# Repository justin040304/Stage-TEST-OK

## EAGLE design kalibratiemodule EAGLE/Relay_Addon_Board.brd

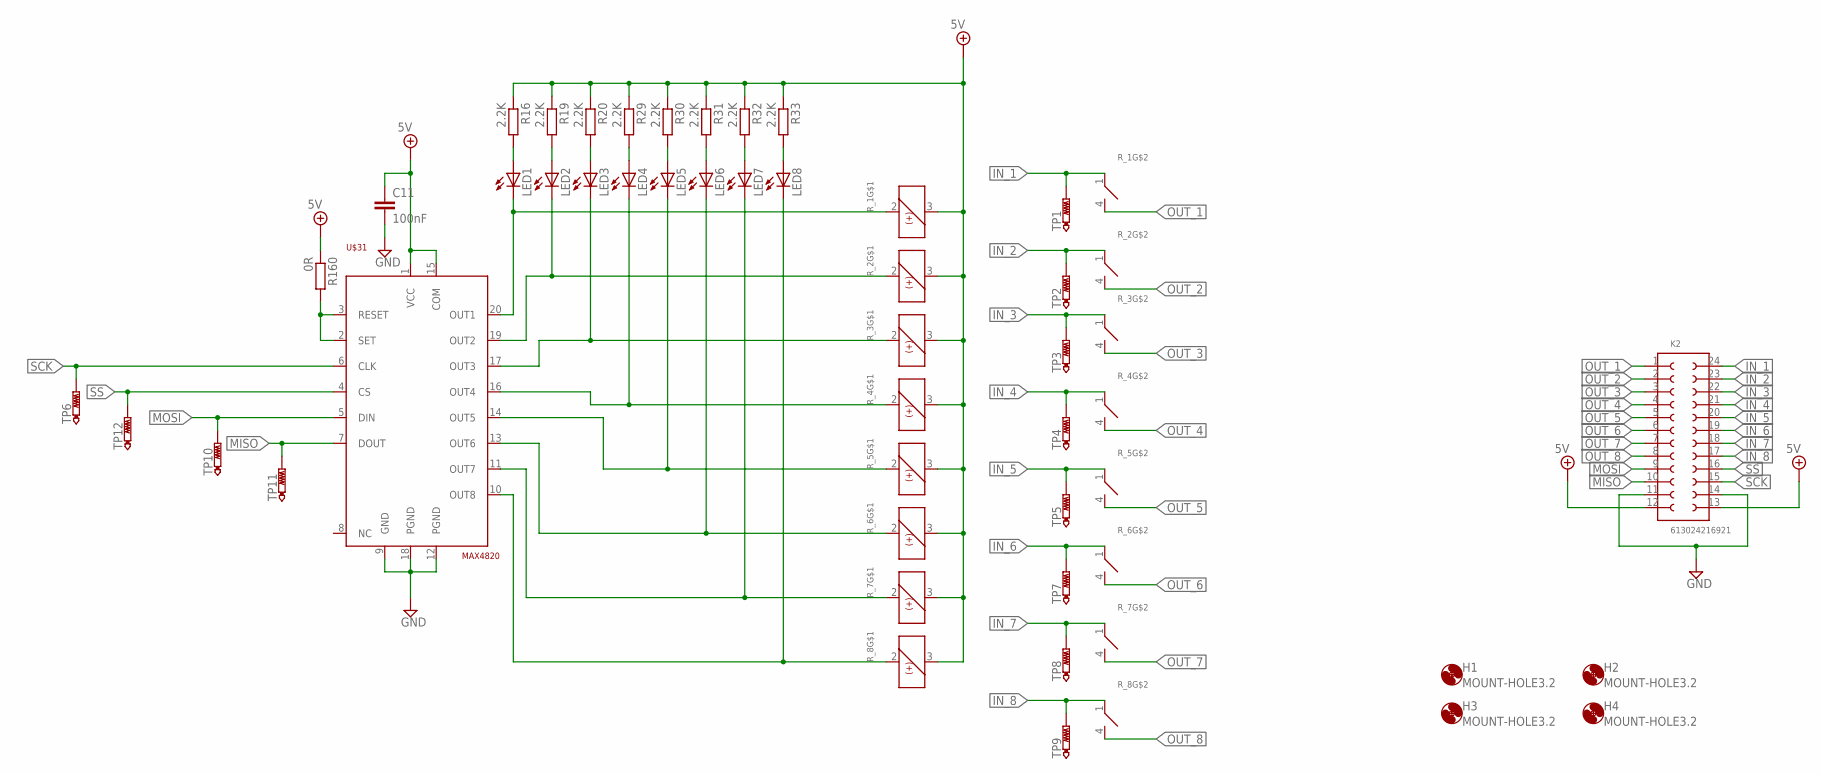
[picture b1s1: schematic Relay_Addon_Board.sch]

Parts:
C11: 100nF; C0603
H1, H2, H3, H4: MOUNT-HOLE3.2; 3,2
K2: 613024216921
LED1, LED2, LED3, LED4, LED5, LED6, LED7, LED8: LEDCHIPLED_0805; CHIPLED_0805
R16, R19, R20, R29, R30, R31, R32, R33: 2.2K; R0603
R160: 0R; R0603
R_1, R_2, R_3, R_4, R_5, R_6, R_7, R_8: 9007-05-01; 9007
TP1, TP2, TP3, TP4, TP5, TP6, TP7, TP8, TP9, TP10, TP11, TP12: PTR1B1,27; B1,27
U$31: MAX4820; TSSOP20

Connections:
5V: C11.1, K2.12, K2.13, R16.1, R19.1, R20.1, R29.1, R30.1, R31.1, R32.1, R33.1, R160.1, R_1.3, R_2.3, R_3.3, R_4.3, R_5.3, R_6.3, R_7.3, R_8.3, U$31.1 (VCC), U$31.15 (COM)
GND: C11.2, K2.11, K2.14, U$31.9 (GND), U$31.12 (PGND), U$31.18 (PGND)
IN_1: K2.24, R_1.1, TP1.TP
IN_2: K2.23, R_2.1, TP2.TP
IN_3: K2.22, R_3.1, TP3.TP
IN_4: K2.21, R_4.1, TP4.TP
IN_5: K2.20, R_5.1, TP5.TP
IN_6: K2.19, R_6.1, TP7.TP
IN_7: K2.18, R_7.1, TP8.TP
IN_8: K2.17, R_8.1, TP9.TP
MISO: K2.10, TP11.TP, U$31.7 (DOUT)
MOSI: K2.9, TP10.TP, U$31.5 (DIN)
unnamed: LED1.A, R16.2
unnamed: LED2.A, R19.2
unnamed: LED3.A, R20.2
unnamed: LED1.C, R_1.2, U$31.20 (OUT1)
unnamed: LED4.A, R29.2
unnamed: LED5.A, R30.2
unnamed: LED7.C, R_7.2, U$31.11 (OUT7)
unnamed: LED6.C, R_6.2, U$31.13 (OUT6)
unnamed: LED5.C, R_5.2, U$31.14 (OUT5)
unnamed: LED2.C, R_2.2, U$31.19 (OUT2)
unnamed: LED3.C, R_3.2, U$31.17 (OUT3)
unnamed: LED4.C, R_4.2, U$31.16 (OUT4)
unnamed: LED8.C, R_8.2, U$31.10 (OUT8)
unnamed: LED8.A, R33.2
unnamed: R160.2, U$31.2 (SET), U$31.3 (RESET)
unnamed: LED7.A, R32.2
unnamed: LED6.A, R31.2
OUT_1: K2.1, R_1.4
OUT_2: K2.2, R_2.4
OUT_3: K2.3, R_3.4
OUT_4: K2.4, R_4.4
OUT_5: K2.5, R_5.4
OUT_6: K2.6, R_6.4
OUT_7: K2.7, R_7.4
OUT_8: K2.8, R_8.4
SCK: K2.15, TP6.TP, U$31.6 (CLK)
SS: K2.16, TP12.TP, U$31.4 (CS)

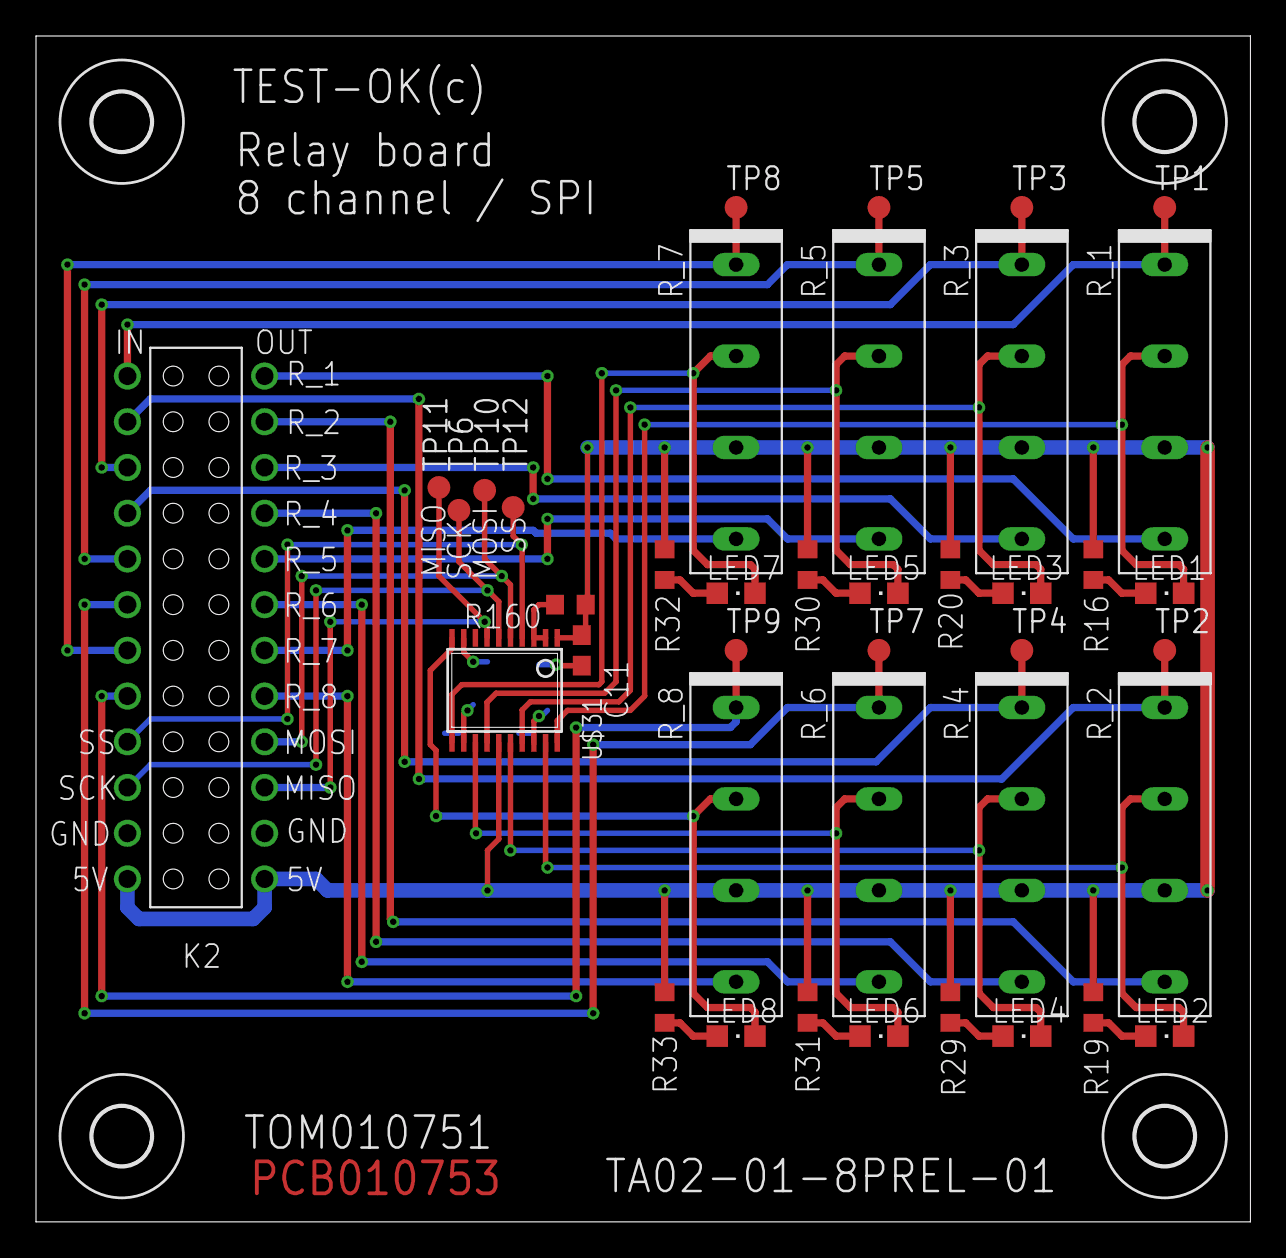
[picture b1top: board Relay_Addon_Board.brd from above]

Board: 2 copper layers, 67.5 x 65.9 mm, 44 parts (0 on the bottom side), 39 nets.

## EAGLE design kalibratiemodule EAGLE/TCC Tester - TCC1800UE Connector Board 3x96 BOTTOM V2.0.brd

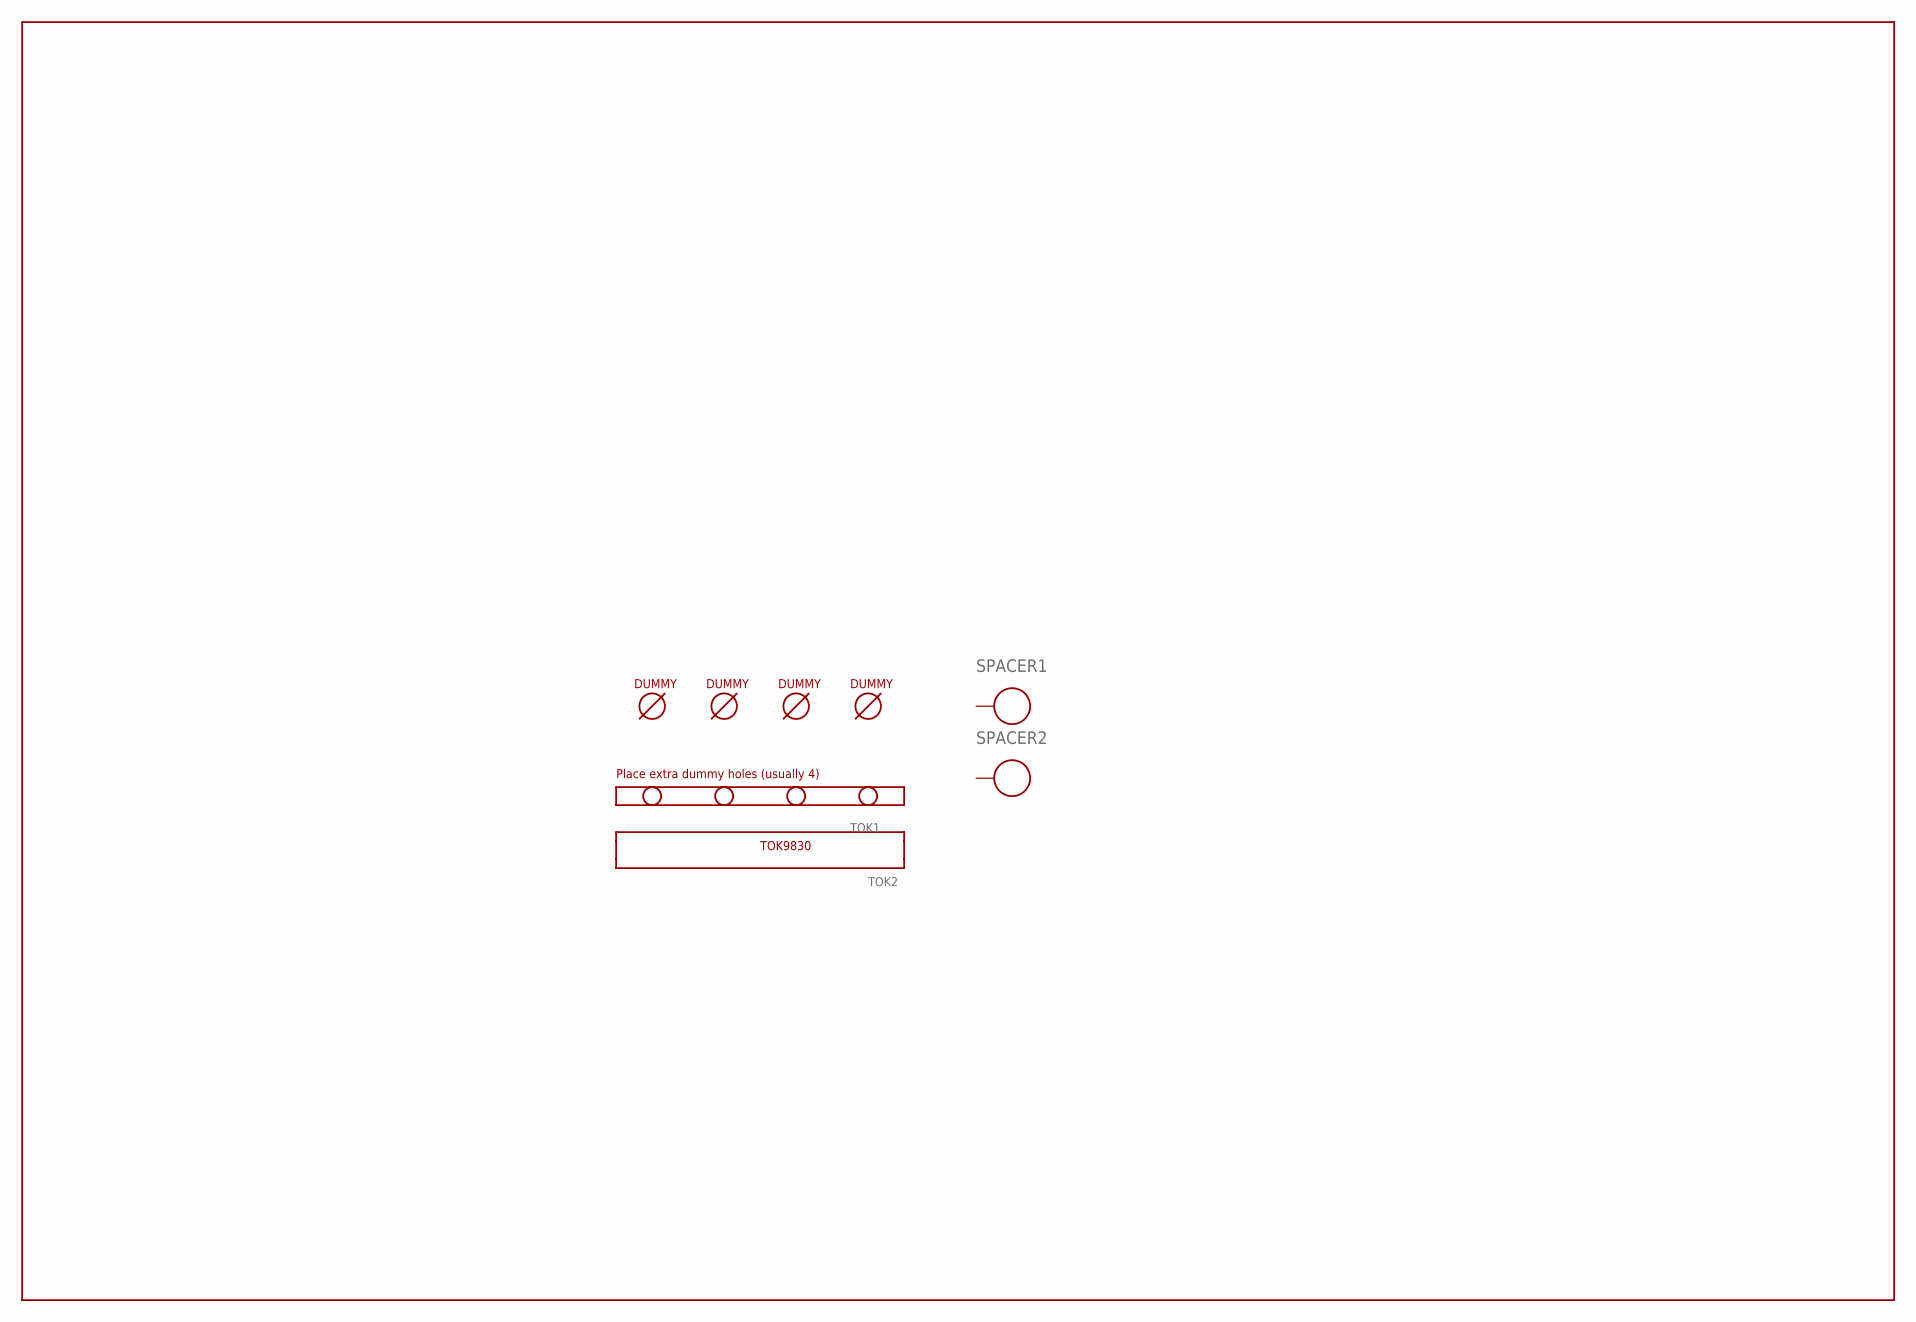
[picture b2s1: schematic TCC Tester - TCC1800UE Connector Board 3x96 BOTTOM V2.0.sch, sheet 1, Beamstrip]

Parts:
SPACER1, SPACER2: WA-SMSI_9774360; WA-SMSI_9774***360
TOK1: BEAMSTRIP_TOK9831_CON; BEAM-STRIP_TOK9831_CON
TOK2: BEAM_TOK9830_CON
U$28, U$29, U$30, U$31: BEAMSTRIP_HOLES_CON; BEAMSTRIP_HOLE_CON

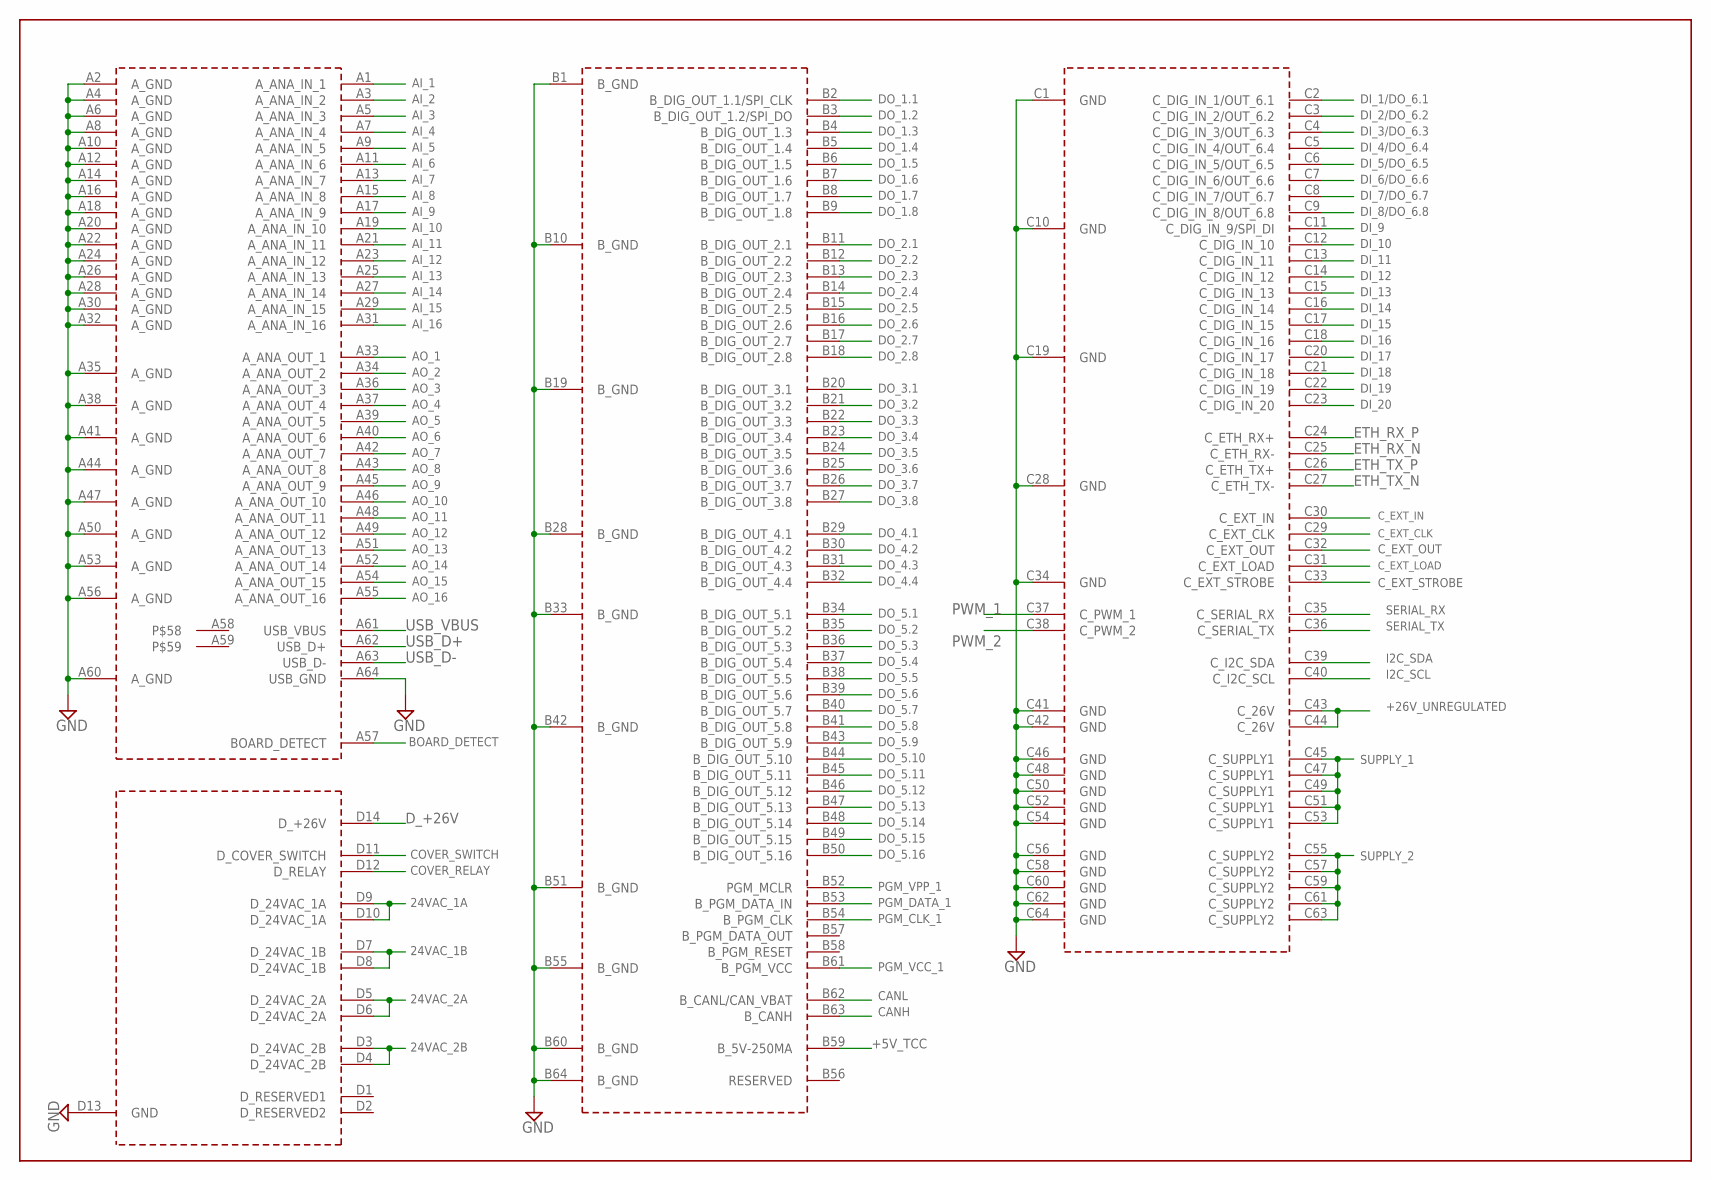
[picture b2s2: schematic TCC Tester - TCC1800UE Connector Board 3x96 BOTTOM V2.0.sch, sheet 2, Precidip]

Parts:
TCC1800UE: TCC1800UE+EXPANSIONBOTTOM; PCBPADS_PRECIDIP_288_TESTOK-BOTTOM

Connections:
24VAC_1A: TCC1800UE.D9 (D_24VAC_1A), TCC1800UE.D10 (D_24VAC_1A); also elsewhere on the board
24VAC_1B: TCC1800UE.D7 (D_24VAC_1B), TCC1800UE.D8 (D_24VAC_1B); also elsewhere on the board
24VAC_2A: TCC1800UE.D5 (D_24VAC_2A), TCC1800UE.D6 (D_24VAC_2A); also elsewhere on the board
24VAC_2B: TCC1800UE.D3 (D_24VAC_2B), TCC1800UE.D4 (D_24VAC_2B); also elsewhere on the board
+5V_TCC: TCC1800UE.B59 (B_5V-250MA); also elsewhere on the board
+26V_UNREGULATED: TCC1800UE.C43 (C_26V), TCC1800UE.C44 (C_26V); also elsewhere on the board
AI_1: TCC1800UE.A1 (A_ANA_IN_1); also elsewhere on the board
AI_2: TCC1800UE.A3 (A_ANA_IN_2); also elsewhere on the board
AI_3: TCC1800UE.A5 (A_ANA_IN_3); also elsewhere on the board
AI_4: TCC1800UE.A7 (A_ANA_IN_4); also elsewhere on the board
AI_5: TCC1800UE.A9 (A_ANA_IN_5); also elsewhere on the board
AI_6: TCC1800UE.A11 (A_ANA_IN_6); also elsewhere on the board
AI_7: TCC1800UE.A13 (A_ANA_IN_7); also elsewhere on the board
AI_8: TCC1800UE.A15 (A_ANA_IN_8); also elsewhere on the board
AI_9: TCC1800UE.A17 (A_ANA_IN_9); also elsewhere on the board
AI_10: TCC1800UE.A19 (A_ANA_IN_10); also elsewhere on the board
AI_11: TCC1800UE.A21 (A_ANA_IN_11); also elsewhere on the board
AI_12: TCC1800UE.A23 (A_ANA_IN_12); also elsewhere on the board
AI_13: TCC1800UE.A25 (A_ANA_IN_13); also elsewhere on the board
AI_14: TCC1800UE.A27 (A_ANA_IN_14); also elsewhere on the board
AI_15: TCC1800UE.A29 (A_ANA_IN_15); also elsewhere on the board
AI_16: TCC1800UE.A31 (A_ANA_IN_16); also elsewhere on the board
AO_1: TCC1800UE.A33 (A_ANA_OUT_1); also elsewhere on the board
AO_2: TCC1800UE.A34 (A_ANA_OUT_2); also elsewhere on the board
AO_3: TCC1800UE.A36 (A_ANA_OUT_3); also elsewhere on the board
AO_4: TCC1800UE.A37 (A_ANA_OUT_4); also elsewhere on the board
AO_5: TCC1800UE.A39 (A_ANA_OUT_5); also elsewhere on the board
AO_6: TCC1800UE.A40 (A_ANA_OUT_6); also elsewhere on the board
AO_7: TCC1800UE.A42 (A_ANA_OUT_7); also elsewhere on the board
AO_8: TCC1800UE.A43 (A_ANA_OUT_8); also elsewhere on the board
AO_9: TCC1800UE.A45 (A_ANA_OUT_9); also elsewhere on the board
AO_10: TCC1800UE.A46 (A_ANA_OUT_10); also elsewhere on the board
AO_11: TCC1800UE.A48 (A_ANA_OUT_11); also elsewhere on the board
AO_12: TCC1800UE.A49 (A_ANA_OUT_12); also elsewhere on the board
AO_13: TCC1800UE.A51 (A_ANA_OUT_13); also elsewhere on the board
AO_14: TCC1800UE.A52 (A_ANA_OUT_14); also elsewhere on the board
AO_15: TCC1800UE.A54 (A_ANA_OUT_15); also elsewhere on the board
AO_16: TCC1800UE.A55 (A_ANA_OUT_16); also elsewhere on the board
BOARD_DETECT: TCC1800UE.A57 (BOARD_DETECT); also elsewhere on the board
CANH: TCC1800UE.B63 (B_CANH); also elsewhere on the board
CANL: TCC1800UE.B62 (B_CANL/CAN_VBAT); also elsewhere on the board
COVER_RELAY: TCC1800UE.D12 (D_RELAY); also elsewhere on the board
COVER_SWITCH: TCC1800UE.D11 (D_COVER_SWITCH)
C_EXT_CLK: TCC1800UE.C29 (C_EXT_CLK); also elsewhere on the board
C_EXT_IN: TCC1800UE.C30 (C_EXT_IN); also elsewhere on the board
C_EXT_LOAD: TCC1800UE.C31 (C_EXT_LOAD); also elsewhere on the board
C_EXT_OUT: TCC1800UE.C32 (C_EXT_OUT)
C_EXT_STROBE: TCC1800UE.C33 (C_EXT_STROBE)
DI_1/DO_6.1: TCC1800UE.C2 (C_DIG_IN_1/OUT_6.1); also elsewhere on the board
DI_2/DO_6.2: TCC1800UE.C3 (C_DIG_IN_2/OUT_6.2); also elsewhere on the board
DI_3/DO_6.3: TCC1800UE.C4 (C_DIG_IN_3/OUT_6.3); also elsewhere on the board
DI_4/DO_6.4: TCC1800UE.C5 (C_DIG_IN_4/OUT_6.4); also elsewhere on the board
DI_5/DO_6.5: TCC1800UE.C6 (C_DIG_IN_5/OUT_6.5); also elsewhere on the board
DI_6/DO_6.6: TCC1800UE.C7 (C_DIG_IN_6/OUT_6.6); also elsewhere on the board
DI_7/DO_6.7: TCC1800UE.C8 (C_DIG_IN_7/OUT_6.7); also elsewhere on the board
DI_8/DO_6.8: TCC1800UE.C9 (C_DIG_IN_8/OUT_6.8); also elsewhere on the board
DI_9: TCC1800UE.C11 (C_DIG_IN_9/SPI_DI); also elsewhere on the board
DI_10: TCC1800UE.C12 (C_DIG_IN_10); also elsewhere on the board
DI_11: TCC1800UE.C13 (C_DIG_IN_11); also elsewhere on the board
DI_12: TCC1800UE.C14 (C_DIG_IN_12); also elsewhere on the board
DI_13: TCC1800UE.C15 (C_DIG_IN_13); also elsewhere on the board
DI_14: TCC1800UE.C16 (C_DIG_IN_14); also elsewhere on the board
DI_15: TCC1800UE.C17 (C_DIG_IN_15); also elsewhere on the board
DI_16: TCC1800UE.C18 (C_DIG_IN_16); also elsewhere on the board
DI_17: TCC1800UE.C20 (C_DIG_IN_17); also elsewhere on the board
DI_18: TCC1800UE.C21 (C_DIG_IN_18); also elsewhere on the board
DI_19: TCC1800UE.C22 (C_DIG_IN_19); also elsewhere on the board
DI_20: TCC1800UE.C23 (C_DIG_IN_20); also elsewhere on the board
DO_1.1: TCC1800UE.B2 (B_DIG_OUT_1.1/SPI_CLK); also elsewhere on the board
DO_1.2: TCC1800UE.B3 (B_DIG_OUT_1.2/SPI_DO); also elsewhere on the board
DO_1.3: TCC1800UE.B4 (B_DIG_OUT_1.3); also elsewhere on the board
DO_1.4: TCC1800UE.B5 (B_DIG_OUT_1.4); also elsewhere on the board
DO_1.5: TCC1800UE.B6 (B_DIG_OUT_1.5); also elsewhere on the board
DO_1.6: TCC1800UE.B7 (B_DIG_OUT_1.6); also elsewhere on the board
DO_1.7: TCC1800UE.B8 (B_DIG_OUT_1.7); also elsewhere on the board
DO_1.8: TCC1800UE.B9 (B_DIG_OUT_1.8); also elsewhere on the board
DO_2.1: TCC1800UE.B11 (B_DIG_OUT_2.1); also elsewhere on the board
DO_2.2: TCC1800UE.B12 (B_DIG_OUT_2.2); also elsewhere on the board
DO_2.3: TCC1800UE.B13 (B_DIG_OUT_2.3); also elsewhere on the board
DO_2.4: TCC1800UE.B14 (B_DIG_OUT_2.4); also elsewhere on the board
DO_2.5: TCC1800UE.B15 (B_DIG_OUT_2.5); also elsewhere on the board
DO_2.6: TCC1800UE.B16 (B_DIG_OUT_2.6); also elsewhere on the board
DO_2.7: TCC1800UE.B17 (B_DIG_OUT_2.7); also elsewhere on the board
DO_2.8: TCC1800UE.B18 (B_DIG_OUT_2.8); also elsewhere on the board
DO_3.1: TCC1800UE.B20 (B_DIG_OUT_3.1); also elsewhere on the board
DO_3.2: TCC1800UE.B21 (B_DIG_OUT_3.2); also elsewhere on the board
DO_3.3: TCC1800UE.B22 (B_DIG_OUT_3.3); also elsewhere on the board
DO_3.4: TCC1800UE.B23 (B_DIG_OUT_3.4); also elsewhere on the board
DO_3.5: TCC1800UE.B24 (B_DIG_OUT_3.5); also elsewhere on the board
DO_3.6: TCC1800UE.B25 (B_DIG_OUT_3.6); also elsewhere on the board
DO_3.7: TCC1800UE.B26 (B_DIG_OUT_3.7); also elsewhere on the board
DO_3.8: TCC1800UE.B27 (B_DIG_OUT_3.8); also elsewhere on the board
DO_4.1: TCC1800UE.B29 (B_DIG_OUT_4.1); also elsewhere on the board
DO_4.2: TCC1800UE.B30 (B_DIG_OUT_4.2); also elsewhere on the board
DO_4.3: TCC1800UE.B31 (B_DIG_OUT_4.3); also elsewhere on the board
DO_4.4: TCC1800UE.B32 (B_DIG_OUT_4.4); also elsewhere on the board
DO_5.1: TCC1800UE.B34 (B_DIG_OUT_5.1); also elsewhere on the board
DO_5.2: TCC1800UE.B35 (B_DIG_OUT_5.2); also elsewhere on the board
DO_5.3: TCC1800UE.B36 (B_DIG_OUT_5.3); also elsewhere on the board
DO_5.4: TCC1800UE.B37 (B_DIG_OUT_5.4); also elsewhere on the board
DO_5.5: TCC1800UE.B38 (B_DIG_OUT_5.5); also elsewhere on the board
DO_5.6: TCC1800UE.B39 (B_DIG_OUT_5.6); also elsewhere on the board
DO_5.7: TCC1800UE.B40 (B_DIG_OUT_5.7); also elsewhere on the board
DO_5.8: TCC1800UE.B41 (B_DIG_OUT_5.8); also elsewhere on the board
DO_5.9: TCC1800UE.B43 (B_DIG_OUT_5.9); also elsewhere on the board
DO_5.10: TCC1800UE.B44 (B_DIG_OUT_5.10); also elsewhere on the board
DO_5.11: TCC1800UE.B45 (B_DIG_OUT_5.11); also elsewhere on the board
DO_5.12: TCC1800UE.B46 (B_DIG_OUT_5.12); also elsewhere on the board
DO_5.13: TCC1800UE.B47 (B_DIG_OUT_5.13); also elsewhere on the board
DO_5.14: TCC1800UE.B48 (B_DIG_OUT_5.14); also elsewhere on the board
DO_5.15: TCC1800UE.B49 (B_DIG_OUT_5.15); also elsewhere on the board
DO_5.16: TCC1800UE.B50 (B_DIG_OUT_5.16); also elsewhere on the board
D_+26V: TCC1800UE.D14 (D_+26V); also elsewhere on the board
ETH_RX_N: TCC1800UE.C25 (C_ETH_RX-); also elsewhere on the board
ETH_RX_P: TCC1800UE.C24 (C_ETH_RX+); also elsewhere on the board
ETH_TX_N: TCC1800UE.C27 (C_ETH_TX-); also elsewhere on the board
ETH_TX_P: TCC1800UE.C26 (C_ETH_TX+); also elsewhere on the board
GND: TCC1800UE.A2 (A_GND), TCC1800UE.A4 (A_GND), TCC1800UE.A6 (A_GND), TCC1800UE.A8 (A_GND), TCC1800UE.A10 (A_GND), TCC1800UE.A12 (A_GND), TCC1800UE.A14 (A_GND), TCC1800UE.A16 (A_GND), TCC1800UE.A18 (A_GND), TCC1800UE.A20 (A_GND), TCC1800UE.A22 (A_GND), TCC1800UE.A24 (A_GND), TCC1800UE.A26 (A_GND), TCC1800UE.A28 (A_GND), TCC1800UE.A30 (A_GND), TCC1800UE.A32 (A_GND), TCC1800UE.A35 (A_GND), TCC1800UE.A38 (A_GND), TCC1800UE.A41 (A_GND), TCC1800UE.A44 (A_GND), TCC1800UE.A47 (A_GND), TCC1800UE.A50 (A_GND), TCC1800UE.A53 (A_GND), TCC1800UE.A56 (A_GND), TCC1800UE.A60 (A_GND), TCC1800UE.A64 (USB_GND), TCC1800UE.B1 (B_GND), TCC1800UE.B10 (B_GND), TCC1800UE.B19 (B_GND), TCC1800UE.B28 (B_GND), TCC1800UE.B33 (B_GND), TCC1800UE.B42 (B_GND), TCC1800UE.B51 (B_GND), TCC1800UE.B55 (B_GND), TCC1800UE.B60 (B_GND), TCC1800UE.B64 (B_GND), TCC1800UE.C1 (GND), TCC1800UE.C10 (GND), TCC1800UE.C19 (GND), TCC1800UE.C28 (GND), TCC1800UE.C34 (GND), TCC1800UE.C41 (GND), TCC1800UE.C42 (GND), TCC1800UE.C46 (GND), TCC1800UE.C48 (GND), TCC1800UE.C50 (GND), TCC1800UE.C52 (GND), TCC1800UE.C54 (GND), TCC1800UE.C56 (GND), TCC1800UE.C58 (GND), TCC1800UE.C60 (GND), TCC1800UE.C62 (GND), TCC1800UE.C64 (GND), TCC1800UE.D13 (GND); also elsewhere on the board
I2C_SCL: TCC1800UE.C40 (C_I2C_SCL); also elsewhere on the board
I2C_SDA: TCC1800UE.C39 (C_I2C_SDA); also elsewhere on the board
PGM_CLK_1: TCC1800UE.B54 (B_PGM_CLK); also elsewhere on the board
PGM_DATA_1: TCC1800UE.B53 (B_PGM_DATA_IN); also elsewhere on the board
PGM_VCC_1: TCC1800UE.B61 (B_PGM_VCC)
PGM_VPP_1: TCC1800UE.B52 (PGM_MCLR); also elsewhere on the board
PWM_1: TCC1800UE.C37 (C_PWM_1); also elsewhere on the board
PWM_2: TCC1800UE.C38 (C_PWM_2); also elsewhere on the board
SERIAL_RX: TCC1800UE.C35 (C_SERIAL_RX); also elsewhere on the board
SERIAL_TX: TCC1800UE.C36 (C_SERIAL_TX); also elsewhere on the board
SUPPLY_1: TCC1800UE.C45 (C_SUPPLY1), TCC1800UE.C47 (C_SUPPLY1), TCC1800UE.C49 (C_SUPPLY1), TCC1800UE.C51 (C_SUPPLY1), TCC1800UE.C53 (C_SUPPLY1); also elsewhere on the board
SUPPLY_2: TCC1800UE.C55 (C_SUPPLY2), TCC1800UE.C57 (C_SUPPLY2), TCC1800UE.C59 (C_SUPPLY2), TCC1800UE.C61 (C_SUPPLY2), TCC1800UE.C63 (C_SUPPLY2); also elsewhere on the board
USB_D+: TCC1800UE.A62 (USB_D+); also elsewhere on the board
USB_D-: TCC1800UE.A63 (USB_D-); also elsewhere on the board
USB_VBUS: TCC1800UE.A61 (USB_VBUS); also elsewhere on the board

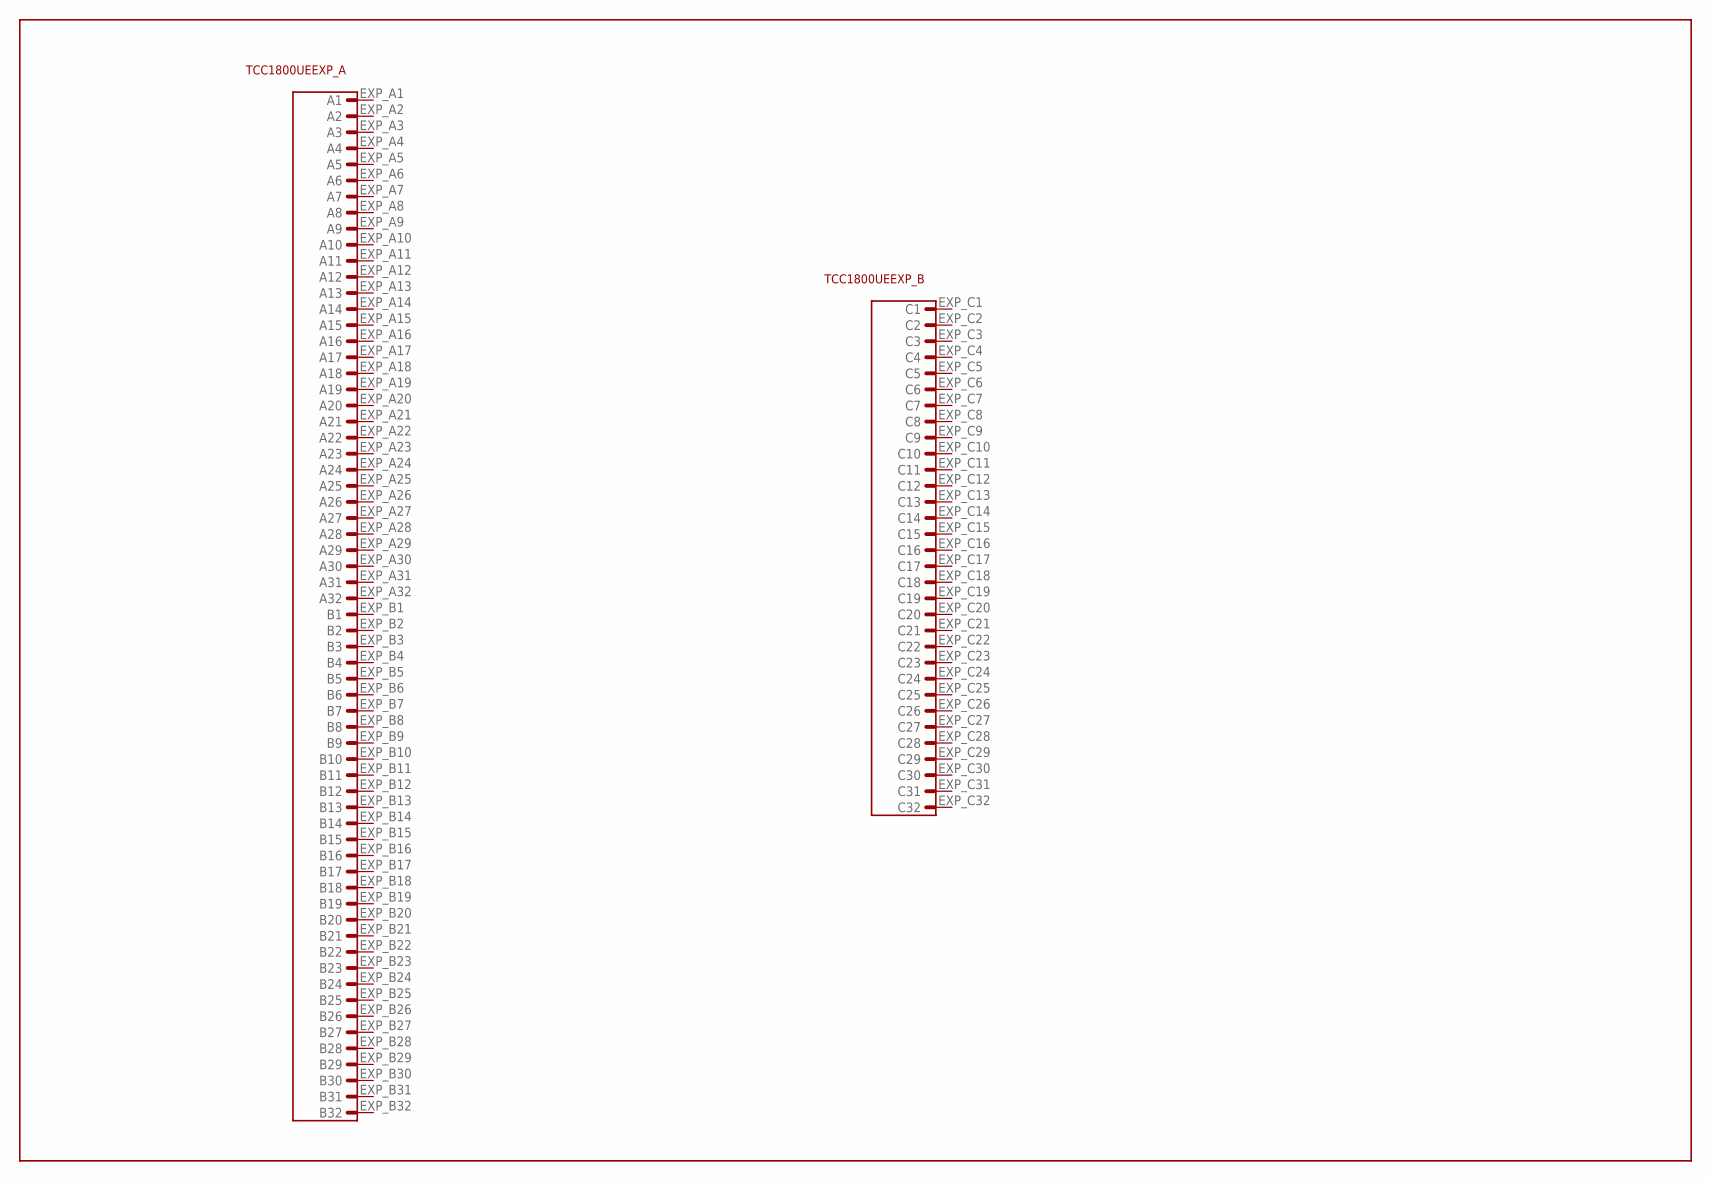
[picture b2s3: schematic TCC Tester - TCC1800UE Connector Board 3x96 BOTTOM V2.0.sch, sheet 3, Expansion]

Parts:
TCC1800UE: TCC1800UE+EXPANSIONBOTTOM; PCBPADS_PRECIDIP_288_TESTOK-BOTTOM

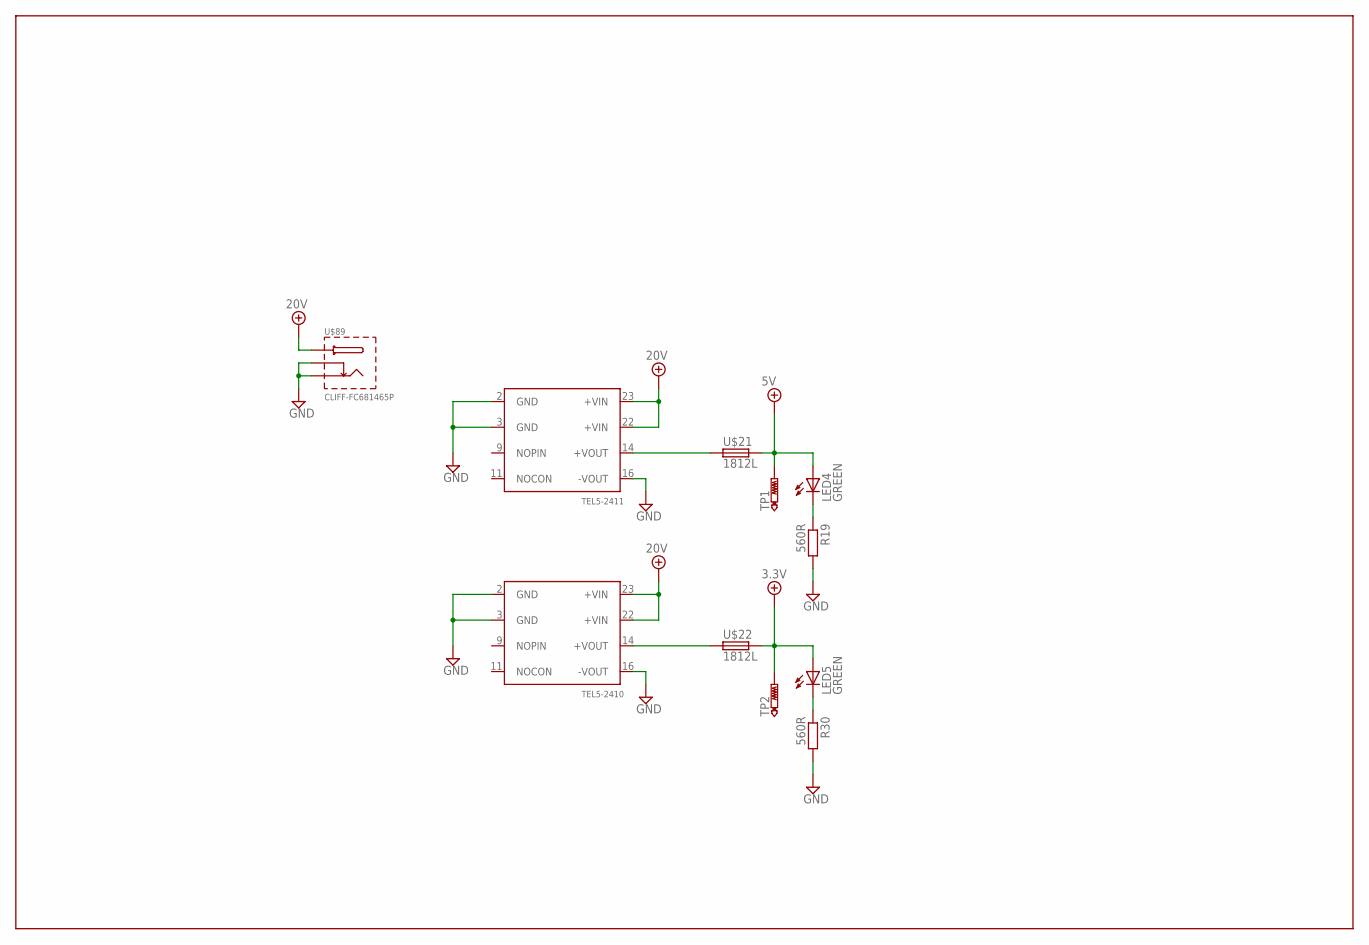
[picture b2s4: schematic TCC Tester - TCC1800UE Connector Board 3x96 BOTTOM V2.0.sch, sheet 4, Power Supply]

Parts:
LED4, LED5: GREEN; CHIPLED_0805
R19, R30: 560R; R0603
TEL5-2410, TEL5-2411: TEL5; TRACO_TEL5_SERIES
TP1, TP2: PTR1TP18R; TP18R
U$21, U$22: 1812L
U$89: CLIFF-FC681465P

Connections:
5V: LED4.A, TP1.TP, U$21.P$2 (2); also elsewhere on the board
20V: TEL5-2410.22 (+VIN), TEL5-2410.23 (+VIN), TEL5-2411.22 (+VIN), TEL5-2411.23 (+VIN), U$89.P$3 (TIP)
+3.3V: LED5.A, TP2.TP, U$22.P$2 (2); also elsewhere on the board
GND: R19.2, R30.2, TEL5-2410.2 (GND), TEL5-2410.3 (GND), TEL5-2410.16 (-VOUT), TEL5-2411.2 (GND), TEL5-2411.3 (GND), TEL5-2411.16 (-VOUT), U$89.P$1 (RING), U$89.P$2 (SWITCH); also elsewhere on the board
unnamed: TEL5-2411.14 (+VOUT), U$21.P$1 (1)
unnamed: TEL5-2410.14 (+VOUT), U$22.P$1 (1)
unnamed: LED4.C, R19.1
unnamed: LED5.C, R30.1

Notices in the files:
parts and their libraries:
Wuerth_Elektronik_eiCan_01_Pin__Socked_H: Copyright: Würth Elektronik
SparkFun-Retired: Licensing:Creative Commons ShareAlike 4.0 International - https://creativecommons.org/licenses/by-sa/4.0
